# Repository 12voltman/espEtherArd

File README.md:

# espEtherArd
General purpose Arduino R3 compatible board based on the ESP32, and with the bonus of ethernet.

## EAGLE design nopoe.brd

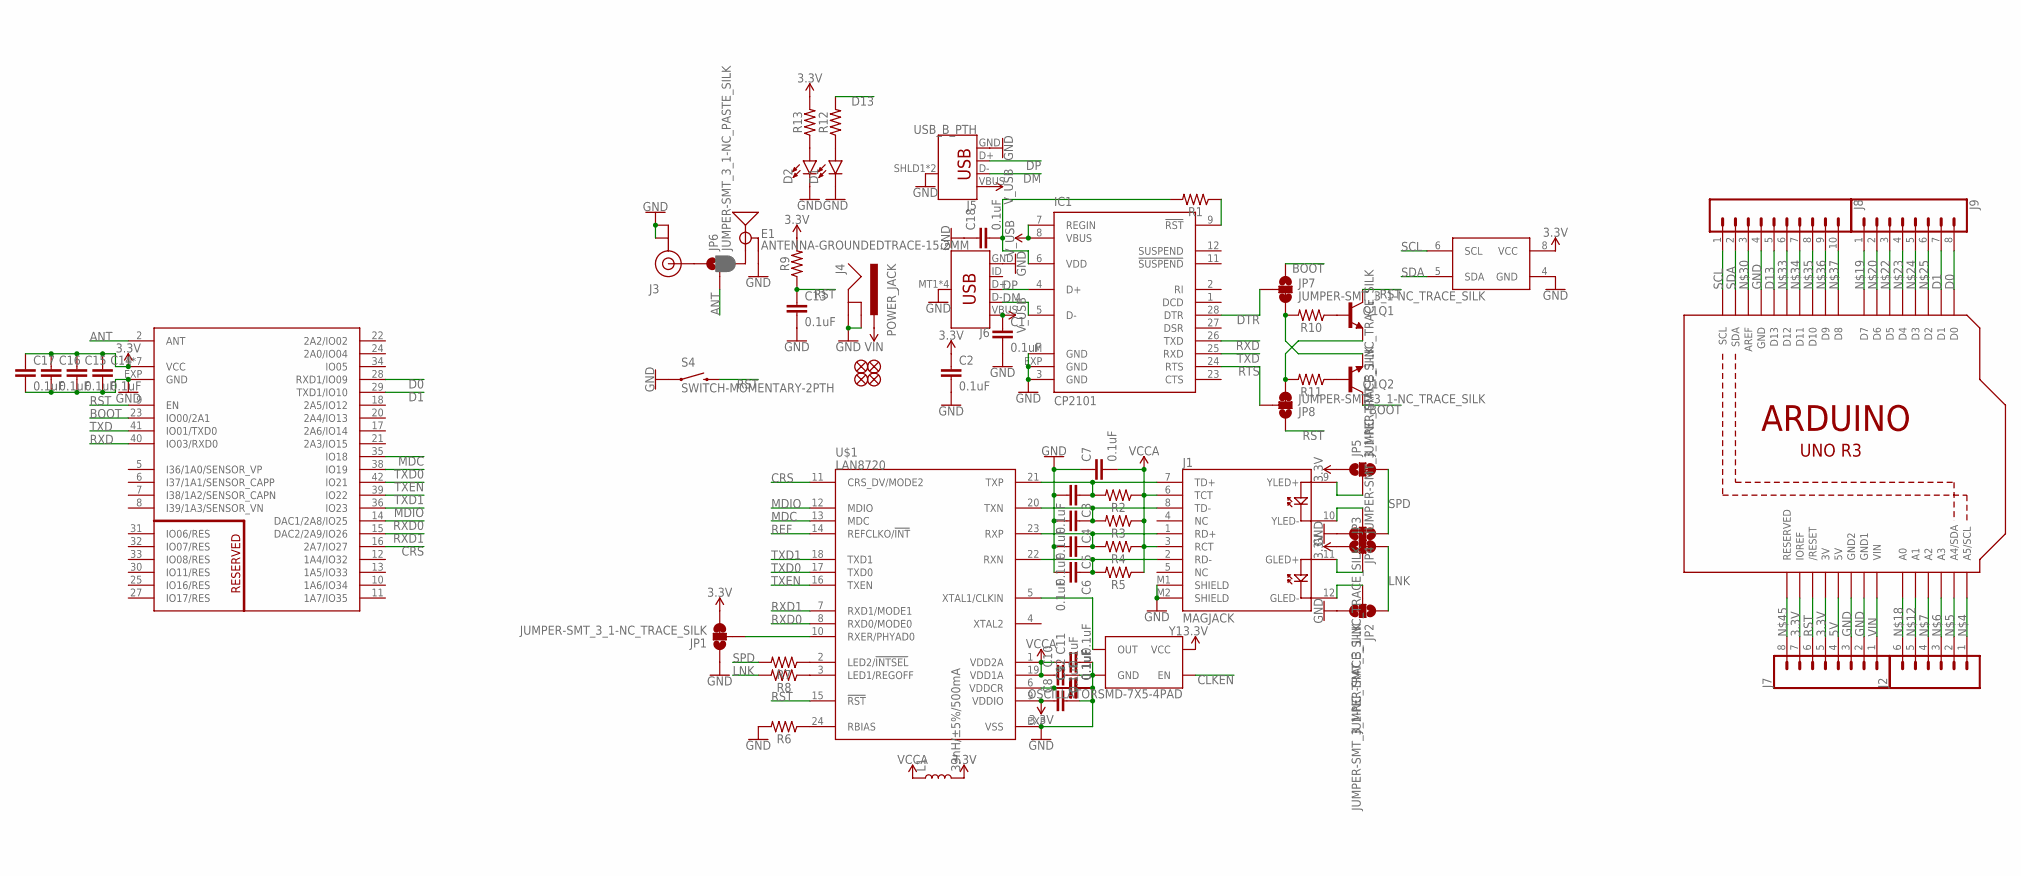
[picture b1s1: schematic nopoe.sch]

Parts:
C1, C2, C3, C4, C5, C6, C7, C8, C9, C10, C11, C12, C13, C14, C15, C16, C17, C18: 0.1uF; 0603
D1, D2: LED0603; LED-0603
E1: ANTENNA-GROUNDEDTRACE-15.2MM; TRACE_ANTENNA_2.4GHZ_15.2MM
FD1, FD2, FD3, FD4: FIDUCIAL1X2; FIDUCIAL-1X2
IC1: CP2101; MLP28
J1: MAGJACK
J2: CONN_06NO_SILK_FEMALE_PTH; 1X06_NO_SILK
J3: U.FL
J4: POWER_JACK; POWER_JACK_PTH
J5: USB_B_PTH; USB-B-PTH
J6: USB_MICRO-B_SMT; USB-MICROB
J7, J9: CONN_08NO_SILK_FEMALE_PTH; 1X08_NO_SILK
J8: CONN_10NO_SILK_PTH_FEMALE; 1X10_NO_SILK
JP1, JP2, JP3, JP4, JP5, JP7, JP8: JUMPER-SMT_3_1-NC_TRACE_SILK; SMT-JUMPER_3_1-NC_TRACE_SILK
JP6: JUMPER-SMT_3_1-NC_PASTE_SILK; SMT-JUMPER_3_1-NC_PASTE_SILK
L1: 33nH/±5%/500mA; 0603
Q1: TRANS_NPN_DUAL-MBT3904DW1T1; SC70-6
R1, R2, R3, R4, R5, R6, R7, R8, R9, R10, R11, R12, R13: 0603
S4: SWITCH-MOMENTARY-2PTH; TACTILE-PTH
U1: ARDUINOR3-DIMENSION; ARDUINOR3
U2: ATSHA204_I2C-SSHDA-*; SOIC-08
U$1: LAN8720; QFN24
U$5: ESP32-PICO-D4; QFN48_7X7
Y1: OSCILLATORSMD-7X5-4PAD; OSCILLATOR-SMD-7X5-4PAD

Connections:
3.3V: C2.1, C8.1, C14.1, C15.1, C16.1, C17.1, J7.5, J7.7, JP1.3, JP3.1, JP5.1, L1.2, R9.2, R13.2, U1.3V, U1.IOREF, U2.8 (VCC), U$1.9 (VDDIO), U$5.1 (VCC), U$5.3 (VCC), U$5.4 (VCC), U$5.19 (VCC), U$5.37 (VCC), U$5.43 (VCC), U$5.46 (VCC), Y1.4 (VCC)
5V: J7.4, U1.5V
ANT: JP6.2, U$5.2 (ANT)
BOOT: JP7.1, Q1.6 (C), U$5.23 (IO00/2A1)
CLKEN: Y1.1 (EN)
CRS: U$1.11 (CRS_DV/MODE2), U$5.16 (2A7/IO27)
D0: J9.8, U1.D0, U$5.28 (RXD1/IO09)
D1: J9.7, U1.D1, U$5.29 (TXD1/IO10)
D13: J8.5, R12.2, U1.D13
DM: IC1.5 (D-), J5.D-, J6.D-
DP: IC1.4 (D+), J5.D+, J6.D+
DTR: IC1.28 (DTR), JP7.2
ECORE: C9.1, C12.1, U$1.6 (VDDCR)
GND: C1.2, C2.2, C3.2, C4.2, C5.2, C6.2, C7.1, C8.2, C9.2, C10.2, C11.2, C12.2, C13.2, C14.2, C15.2, C16.2, C17.2, C18.1, D1.C, D2.C, E1.GND, IC1.3 (GND), IC1.EXP (GND), IC1.M (GND), J1.M1 (SHIELD), J1.M2 (SHIELD), J3.1 (GND), J3.2 (GND), J4.GND, J4.GNDBREAK, J5.GND, J5.SHLD1 (SHIELD), J5.SHLD2 (SHIELD), J6.GND, J6.MT1 (SHIELD), J6.MT2 (SHIELD), J6.P$1 (SHIELD), J6.P$2 (SHIELD), J7.2, J7.3, J8.4, JP1.1, JP2.3, JP4.3, R6.2, S4.1, S4.2 (1), U1.GND, U1.GND1, U1.GND2, U2.4 (GND), U$1.EXP (VSS), U$5.EXP (GND), Y1.2 (GND)
LNK: JP2.1, JP3.3, R8.2
MDC: U$1.13 (MDC), U$5.35 (IO18)
MDIO: U$1.12 (MDIO), U$5.36 (IO23)
unnamed: IC1.9 (!RST), R1.1
unnamed: J2.1, U1.A5 (A5/SCL)
unnamed: J2.2, U1.A4 (A4/SDA)
unnamed: J2.3, U1.A3
unnamed: J2.4, U1.A2
unnamed: J1.12 (GLED-), JP2.2
unnamed: J1.11 (GLED+), JP3.2
unnamed: J1.10 (YLED-), JP4.2
unnamed: J1.9 (YLED+), JP5.2
unnamed: J2.5, U1.A1
unnamed: R7.1, U$1.2 (LED2/!INTSEL)
unnamed: R8.1, U$1.3 (LED1/REGOFF)
unnamed: E1.ANT (SIGNAL), JP6.3
unnamed: J3.FEED (SIGNAL), JP6.1
unnamed: R6.1, U$1.24 (RBIAS)
unnamed: J2.6, U1.A0
unnamed: J9.1, U1.D7
unnamed: J9.2, U1.D6
unnamed: JP1.2, U$1.10 (RXER/PHYAD0)
unnamed: J9.3, U1.D5
unnamed: J9.4, U1.D4
unnamed: J9.5, U1.D3
unnamed: J9.6, U1.D2
unnamed: U$1.5 (XTAL1/CLKIN), Y1.3 (OUT)
unnamed: C18.2, IC1.6 (VDD), R1.2
unnamed: D1.A, R12.1
unnamed: Q1.5 (B), R10.1
unnamed: J8.3, U1.AREF
unnamed: JP7.3, Q1.1 (E), R10.2
unnamed: D2.A, R13.1
unnamed: J8.6, U1.D12
unnamed: J8.7, U1.D11
unnamed: J8.8, U1.D10
unnamed: J8.9, U1.D9
unnamed: J8.10, U1.D8
unnamed: Q1.2 (B), R11.1
unnamed: JP8.3, Q1.4 (E), R11.2
unnamed: J7.8, U1.RESERVED
REF: U$1.14 (REFCLKO/!INT)
RST: C13.1, J7.6, JP8.1, Q1.3 (C), R9.1, S4.3 (2), S4.4 (2), U1.RESET (/RESET), U$1.15 (!RST), U$5.9 (EN)
RTS: IC1.24 (RTS), JP8.2
RXD: IC1.26 (TXD), U$5.40 (IO03/RXD0)
RXD0: U$1.8 (RXD0/MODE0), U$5.14 (DAC1/2A8/IO25)
RXD1: U$1.7 (RXD1/MODE1), U$5.15 (DAC2/2A9/IO26)
RXN: C6.1, J1.2 (RD-), R5.2, U$1.22 (RXN)
RXP: C5.1, J1.1 (RD+), R4.2, U$1.23 (RXP)
SCL: J8.1, U1.SCL, U2.6 (SCL)
SDA: J8.2, U1.SDA, U2.5 (SDA)
SPD: JP4.1, JP5.3, R7.2
TXD: IC1.25 (RXD), U$5.41 (IO01/TXD0)
TXD0: U$1.17 (TXD0), U$5.38 (IO19)
TXD1: U$1.18 (TXD1), U$5.39 (IO22)
TXEN: U$1.16 (TXEN), U$5.42 (IO21)
TXN: C4.1, J1.8 (TD-), R3.2, U$1.20 (TXN)
TXP: C3.1, J1.7 (TD+), R2.2, U$1.21 (TXP)
VCCA: C7.2, C10.1, C11.1, J1.3 (RCT), J1.6 (TCT), L1.1, R2.1, R3.1, R4.1, R5.1, U$1.1 (VDD2A), U$1.19 (VDD1A)
VIN: J4.PWR, J7.1, U1.VIN
V_USB: C1.1, IC1.7 (REGIN), IC1.8 (VBUS), J5.VBUS, J6.VBUS

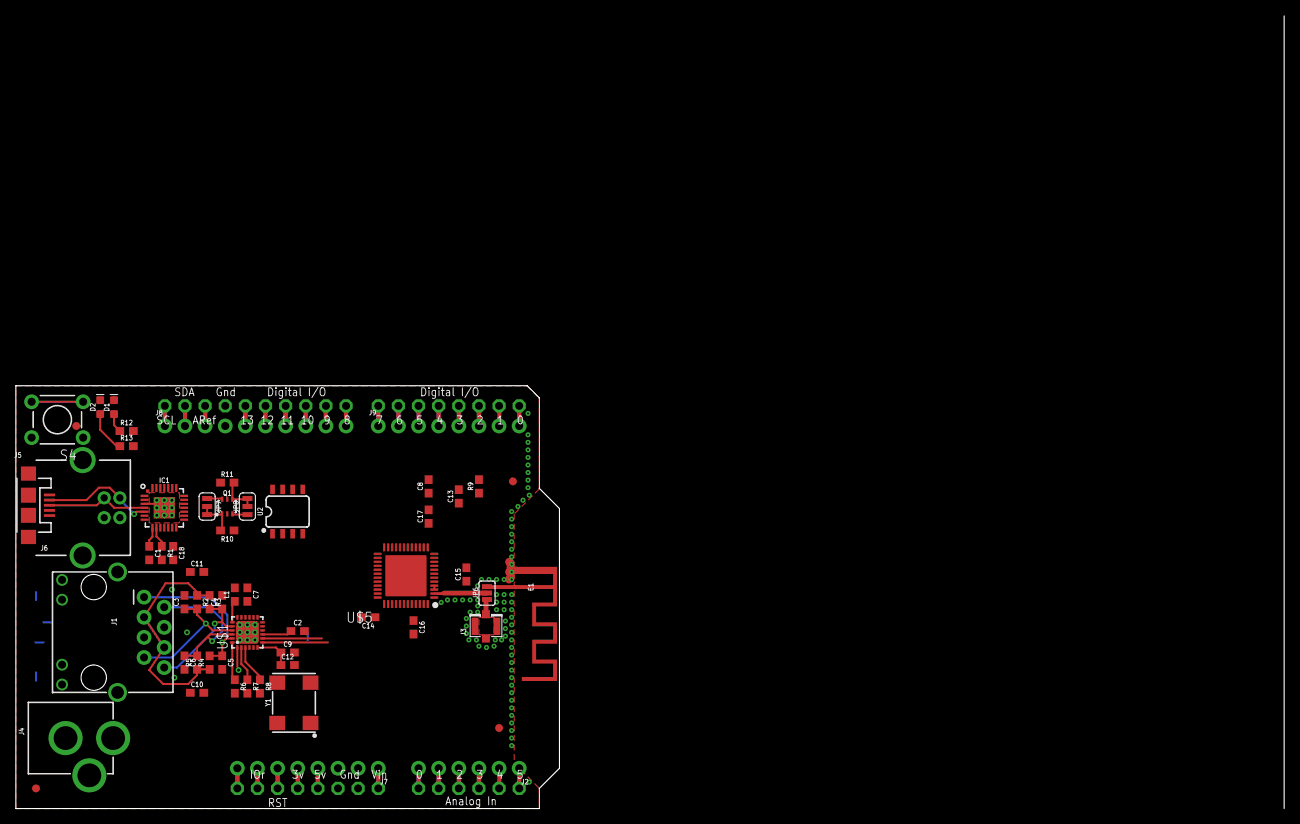
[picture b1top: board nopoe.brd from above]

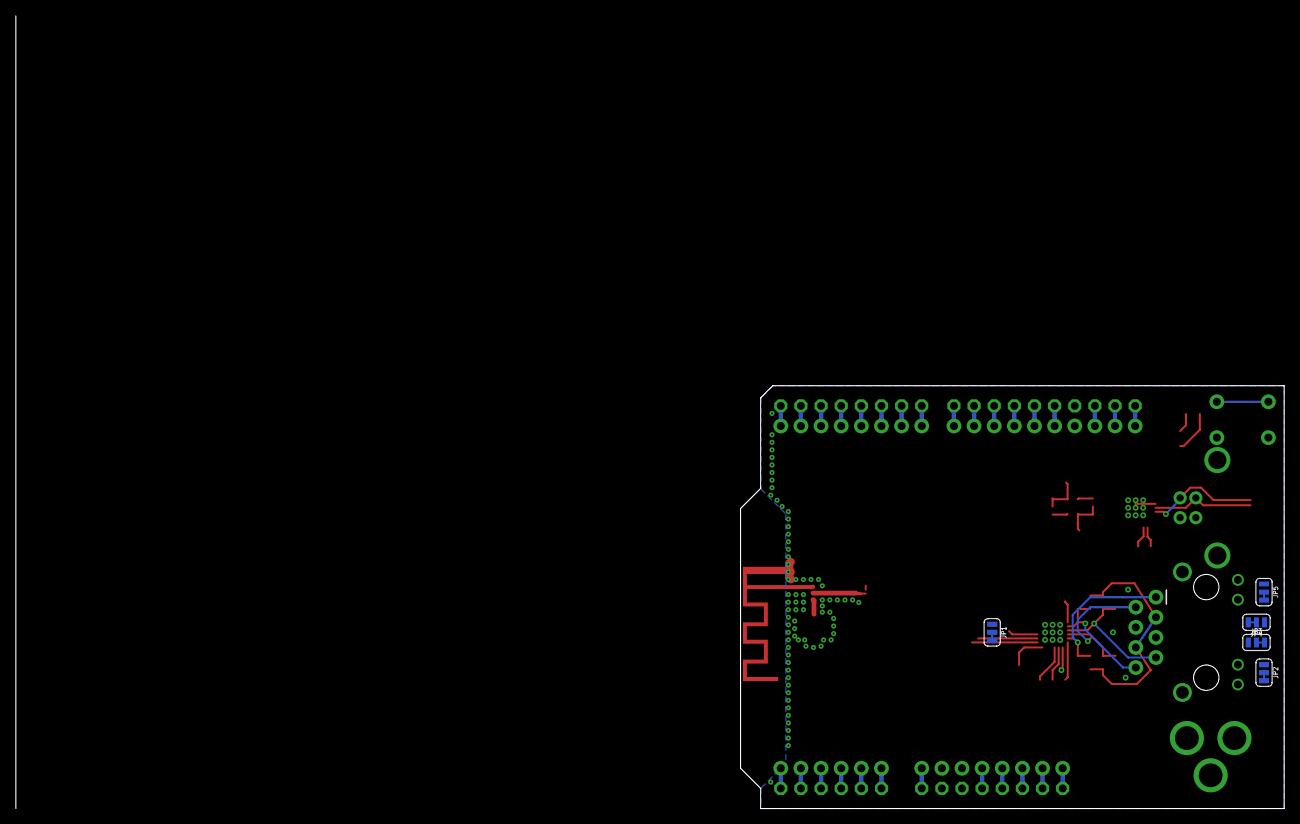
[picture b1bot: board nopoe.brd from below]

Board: 2 copper layers, 160.0 x 100.0 mm, 64 parts (5 on the bottom side), 73 nets.

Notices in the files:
parts and their libraries:
SparkFun-Capacitors: Licensing: Creative Commons ShareAlike 4.0 International - https://creativecommons.org/licenses/by-sa/4.0
microchip-smsc-lan8720: (C) 2014 Tomasz Boleslaw CEDRO, cederom@tlen.pl, http://www.tomek.cedro.info.
